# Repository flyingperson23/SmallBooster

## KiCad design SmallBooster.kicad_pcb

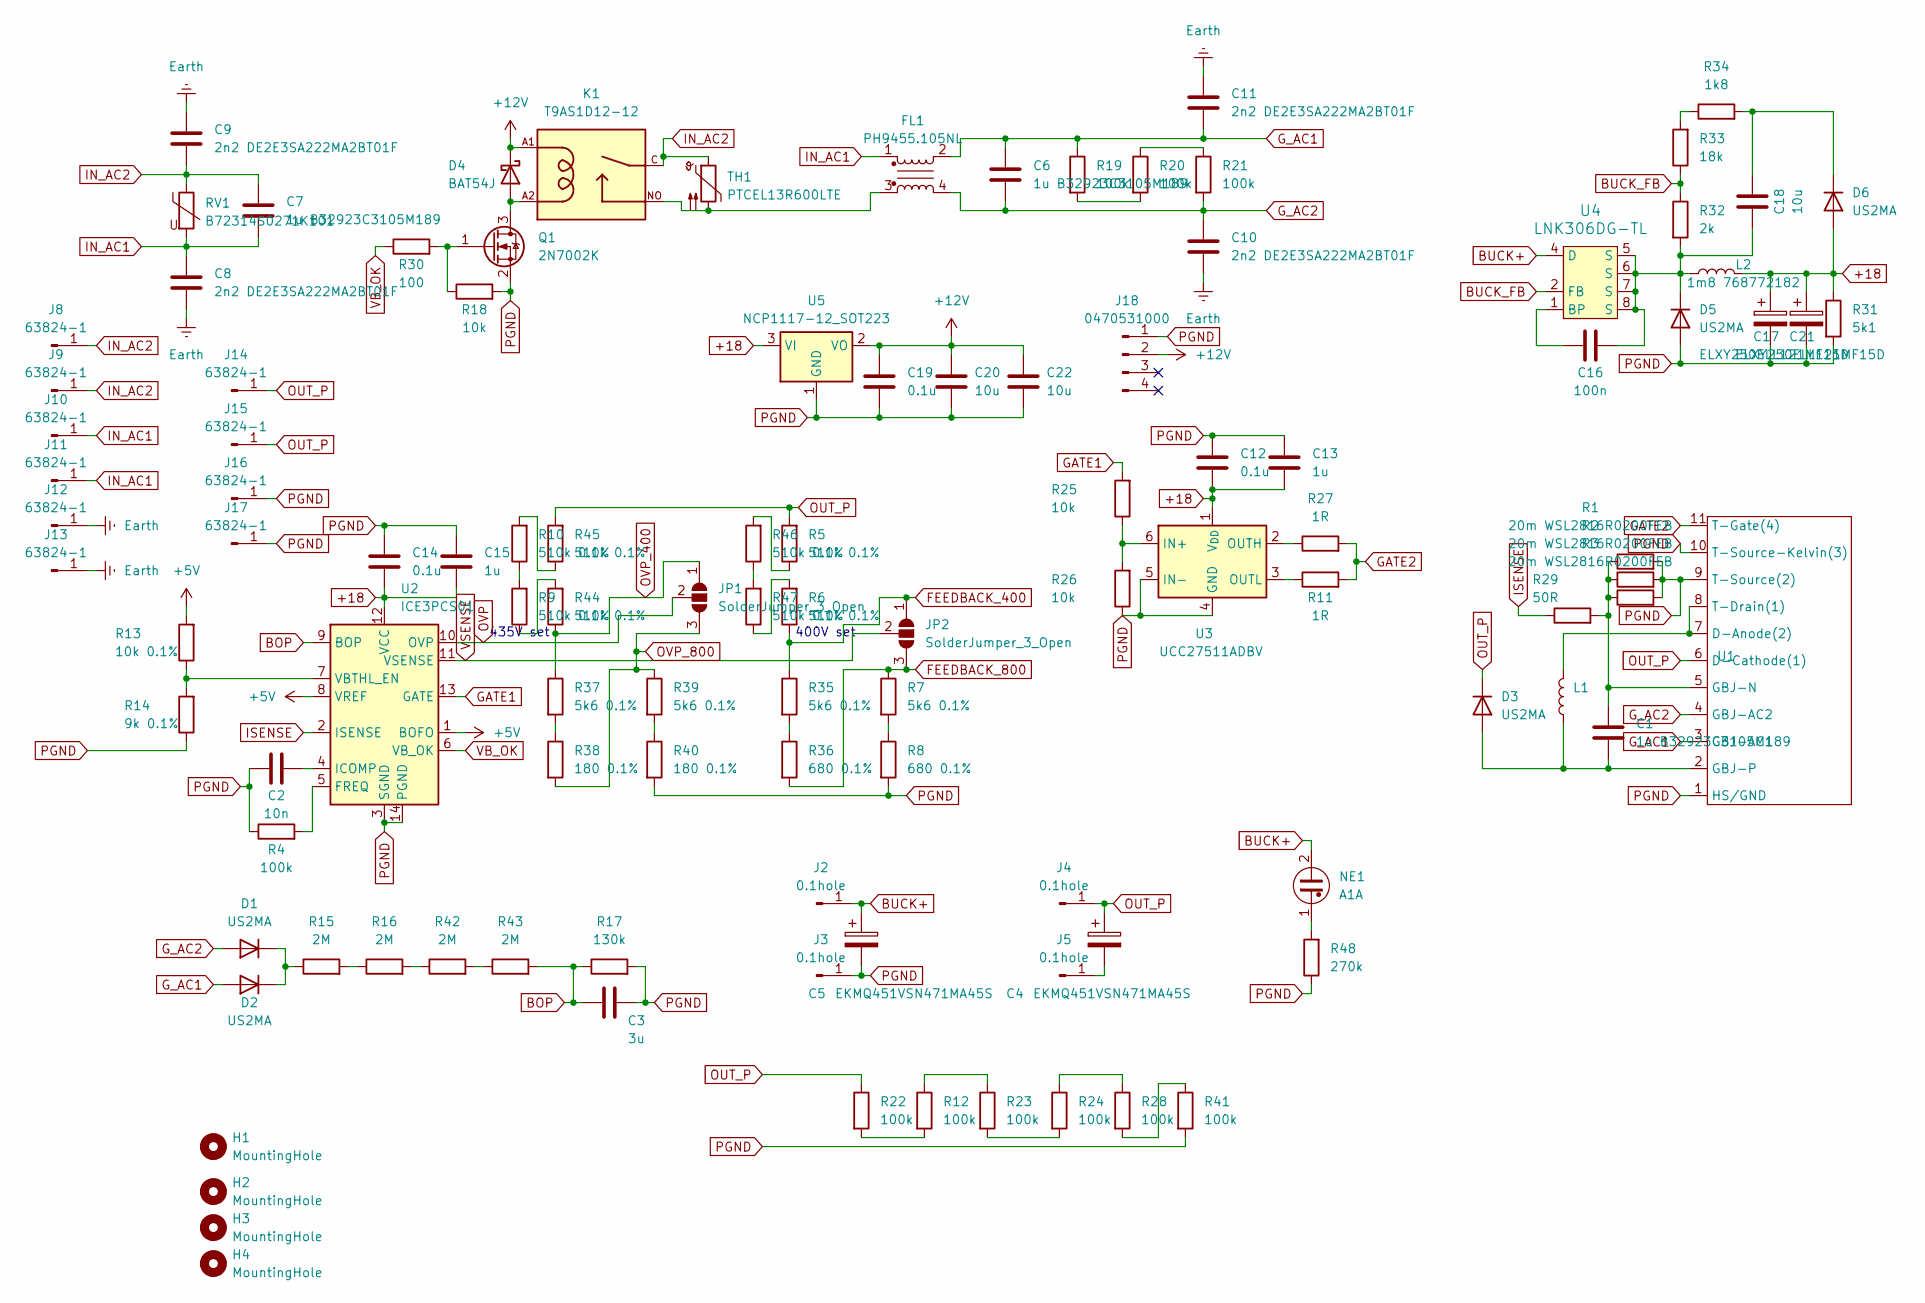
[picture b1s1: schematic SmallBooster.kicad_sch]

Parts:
C1, C6, C7: 1u B32923C3105M189; B32923C__26.5_x_12_
C2: 10n; C_0603_1608Metric
C3: 3u; C_0603_1608Metric
C4, C5: EKMQ451VSN471MA45S; CAPPRD1000W180D3550H4700
C8, C9, C10, C11: 2n2 DE2E3SA222MA2BT01F; CAP_DE2E3SA222MA2BT01F
C12, C14, C19: 0.1u; C_0603_1608Metric
C13, C15: 1u; C_0603_1608Metric
C16: 100n; C_0603_1608Metric
C17, C21: ELXY250ELL121MF15D; CHEMI-F15
C18, C20, C22: 10u; C_0603_1608Metric
D1, D2, D3, D5, D6: US2MA; D_SMA
D4: BAT54J; D_SOD-323F
FL1: PH9455.105NL
H1, H2, H3, H4: MountingHole; MountingHole_3.2mm_M3
J2, J3, J4, J5: 0.1hole
J8, J9, J10, J11, J12, J13, J14, J15, J16, J17: 63824-1; Spade 63824-1
J18: 0470531000; CONN_SD-47053-001_H10p00_MOL
JP1, JP2: SolderJumper_3_Open; SolderJumper-3_P1.3mm_Open_Pad1.0x1.5mm
K1: T9AS1D12-12; TE_1-1393210-3; PARTREV 0815
L1: 0074439A7 40t 14awg; 0074439A7
L2: 1m8 768772182; WE-TI_809591
NE1: A1A; NEON-A1A
Q1: 2N7002K; SOT-23
R1, R2, R3: 20m WSL2816R0200FEB; R_2816_7142Metric
R4: 100k; R_0603_1608Metric
R5, R6, R9, R10, R44, R45, R46, R47: 510k 0.1%; R_1206_3216Metric
R7, R35, R37, R39: 5k6 0.1%; R_0603_1608Metric
R8, R36: 680 0.1%; R_0603_1608Metric
R11, R27: 1R; R_0603_1608Metric
R12, R19, R20, R21, R22, R23, R24, R28, R41: 100k; R_0805_2012Metric
R13: 10k 0.1%; R_0603_1608Metric
R14: 9k 0.1%; R_0603_1608Metric
R15, R16, R42, R43: 2M; C_0805_2012Metric
R17: 130k; R_0603_1608Metric
R18, R25, R26: 10k; R_0603_1608Metric
R29: 50R; R_0603_1608Metric
R30: 100; R_0603_1608Metric
R31: 5k1; R_0603_1608Metric
R32: 2k; R_0603_1608Metric
R33: 18k; R_0603_1608Metric
R34: 1k8; R_0603_1608Metric
R38, R40: 180 0.1%; R_0603_1608Metric
R48: 270k; R_Axial_DIN0207_L6.3mm_D2.5mm_P5.08mm_Vertical
RV1: B72314S0271K101
TH1: PTCEL13R600LTE; THERMISTOR_PTCEL13_5MM_VIS
U1: C40-058-VE+GBJ+TO247-2+TO247-4
U2: ICE3PCS01; SOIC-14_3.9x8.7mm_P1.27mm
U3: UCC27511ADBV; SOT-23-6
U4: LNK306DG-TL; SOIC-7-8_W3.9mm; MPN LNK306DG-TL; Digi-Key_PN 596-1239-1-ND
U5: NCP1117-12_SOT223; SOT-223-3_TabPin2

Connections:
+5V: R13.2, U2.1 (BOFO), U2.8 (VREF)
+12V: C19.1, C20.2, C22.2, D4.1 (K), J18.2, K1.A1, U5.2 (VO)
+18: C12.2, C13.2, C14.2, C15.2, C17.1, C21.1, D6.2 (A), L2.2, R31.1, U2.12 (VCC), U3.1 (V_{DD}), U5.3 (VI)
BOP: C3.1, R17.1, R43.2, U2.9 (BOP)
BUCK+: C5.1, J2.1, NE1.2, U4.4 (D)
BUCK_FB: R32.1, R33.1, U4.2 (FB)
Earth: C8.2, C9.1, C10.2, C11.1, J12.1, J13.1
FEEDBACK_400: JP2.1 (A), R6.1, R35.1
FEEDBACK_800: JP2.3 (B), R7.1, R36.2
GATE1: R25.2, U2.13 (GATE)
GATE2: R11.2, R27.2, U1.11 (T-Gate(4))
G_AC1: C6.1, C11.2, D2.2 (A), FL1.2, R19.1, U1.3 (GBJ-AC1)
G_AC2: C6.2, C10.1, D1.2 (A), FL1.4, R21.2, U1.4 (GBJ-AC2)
IN_AC1: C7.2, C8.1, FL1.1, J10.1, J11.1, RV1.2
IN_AC2: C7.1, C9.2, J8.1, J9.1, K1.C, RV1.1, TH1.1
ISENSE: R29.1, U2.2 (ISENSE)
unnamed: D1.1 (K), D2.1 (K), R15.1
unnamed: C1.2, D3.2 (A), L1.1, U1.2 (GBJ-P)
unnamed: D4.2 (A), K1.A2, Q1.3 (D)
unnamed: C16.2, C18.1, D5.1 (K), L2.1, R32.2, U4.5 (S), U4.6 (S), U4.7 (S), U4.8 (S)
unnamed: C18.2, D6.1 (K), R34.2
unnamed: FL1.3, K1.NO, TH1.2
unnamed: C4.2, J5.1
unnamed: NE1.1, R48.2
unnamed: Q1.1 (G), R18.1, R30.2
unnamed: R7.2, R8.1
unnamed: R9.2, R10.1
unnamed: R10.2, R45.1
unnamed: R12.1, R23.1
unnamed: R12.2, R22.2
unnamed: R15.2, R16.1
unnamed: R16.2, R42.1
unnamed: R19.2, R20.2
unnamed: R20.1, R21.1
unnamed: R23.2, R24.2
unnamed: R24.1, R28.1
unnamed: R28.2, R41.1
unnamed: R33.2, R34.1
unnamed: R35.2, R36.1
unnamed: R37.2, R38.1
unnamed: R39.2, R40.1
unnamed: R42.2, R43.1
unnamed: R9.1, R44.2
unnamed: R46.1, R47.2
unnamed: R5.1, R46.2
unnamed: R6.2, R47.1
unnamed: L1.2, U1.7 (D-Anode(2)), U1.8 (T-Drain(1))
unnamed: C1.1, R1.1, R2.1, R3.1, R29.2, U1.5 (GBJ-N)
unnamed: R4.2, U2.5 (FREQ)
unnamed: C2.2, U2.4 (ICOMP)
unnamed: R13.1, R14.2, U2.7 (VBTHL_EN)
unnamed: R25.1, R26.2, U3.6 (IN+)
unnamed: R27.1, U3.2 (OUTH)
unnamed: R11.1, U3.3 (OUTL)
unnamed: C16.1, U4.1 (BP)
OUT_P: C4.1, D3.1 (K), J4.1, J14.1, J15.1, R5.2, R22.1, R45.2, U1.6 (D-Cathode(1))
OVP: JP1.2 (C), U2.10 (OVP)
OVP_400: JP1.1 (A), R37.1, R44.1
OVP_800: JP1.3 (B), R38.2, R39.1
PGND: C2.1, C3.2, C5.2, C12.1, C13.1, C14.1, C15.1, C17.2, C19.2, C20.1, C21.2, C22.1, D5.2 (A), J3.1, J16.1, J17.1, J18.1, Q1.2 (S), R1.2, R2.2, R3.2, R4.1, R8.2, R14.1, R17.2, R18.2, R26.1, R31.2, R40.2, R41.2, R48.1, U1.1 (HS/GND), U1.9 (T-Source(2)), U1.10 (T-Source-Kelvin(3)), U2.3 (SGND), U2.14 (PGND), U3.4 (GND), U3.5 (IN-), U5.1 (GND)
VB_OK: R30.1, U2.6 (VB_OK)
VSENSE: JP2.2 (C), U2.11 (VSENSE)

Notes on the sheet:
400V set
435V set

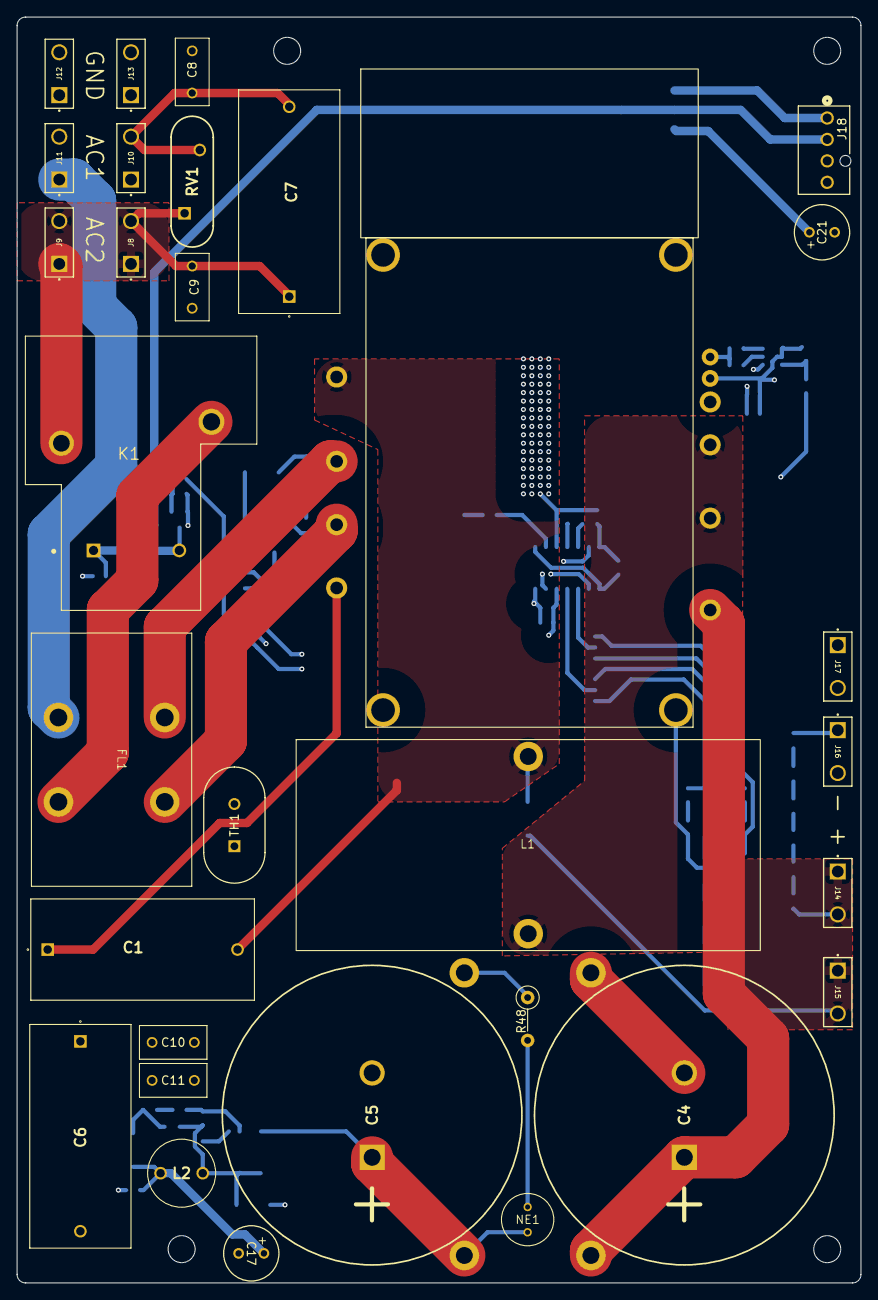
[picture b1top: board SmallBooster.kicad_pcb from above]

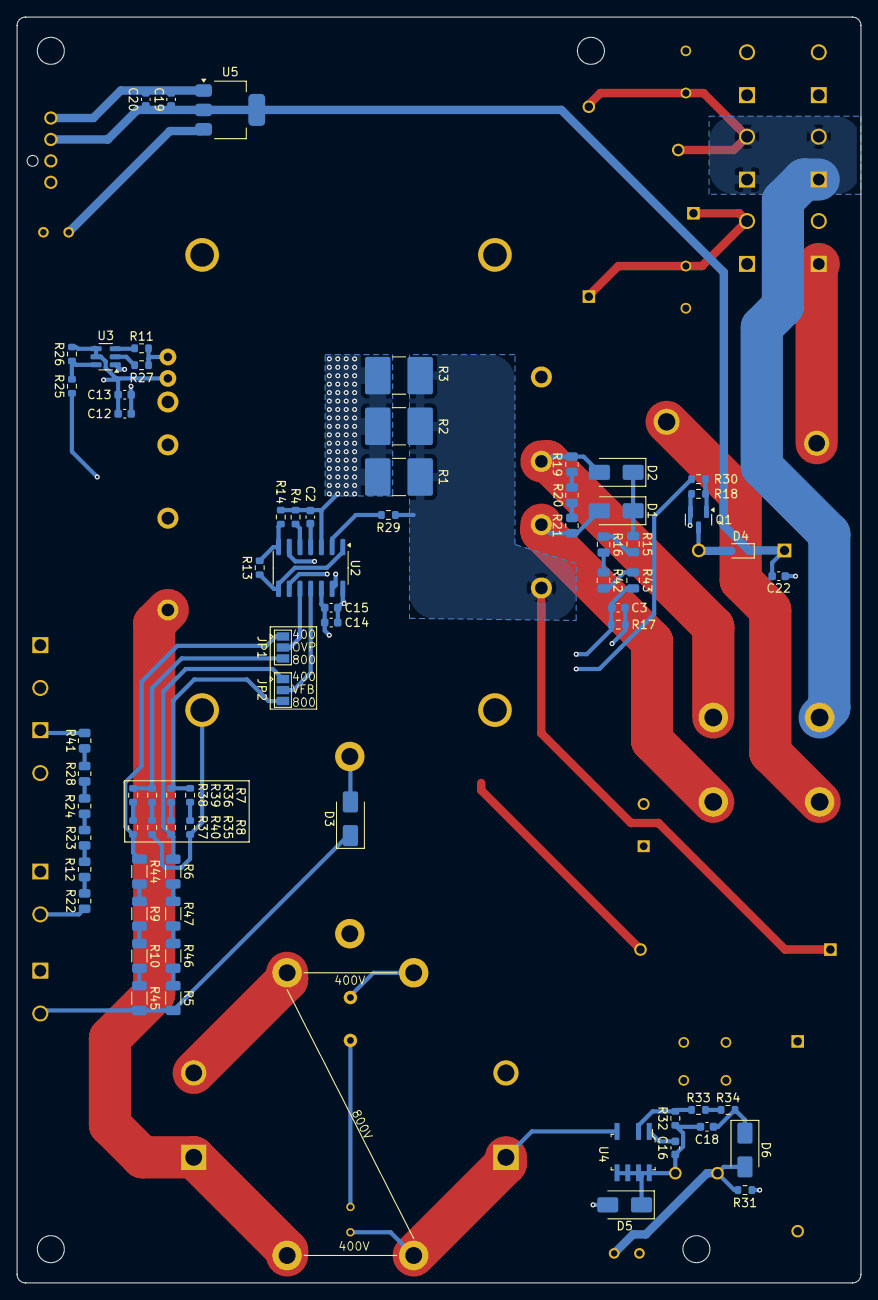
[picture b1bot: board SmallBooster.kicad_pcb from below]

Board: 4 copper layers, 100.0 x 150.0 mm, 110 parts (71 on the bottom side), 62 nets.

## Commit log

2024-10-11 v1 done?
